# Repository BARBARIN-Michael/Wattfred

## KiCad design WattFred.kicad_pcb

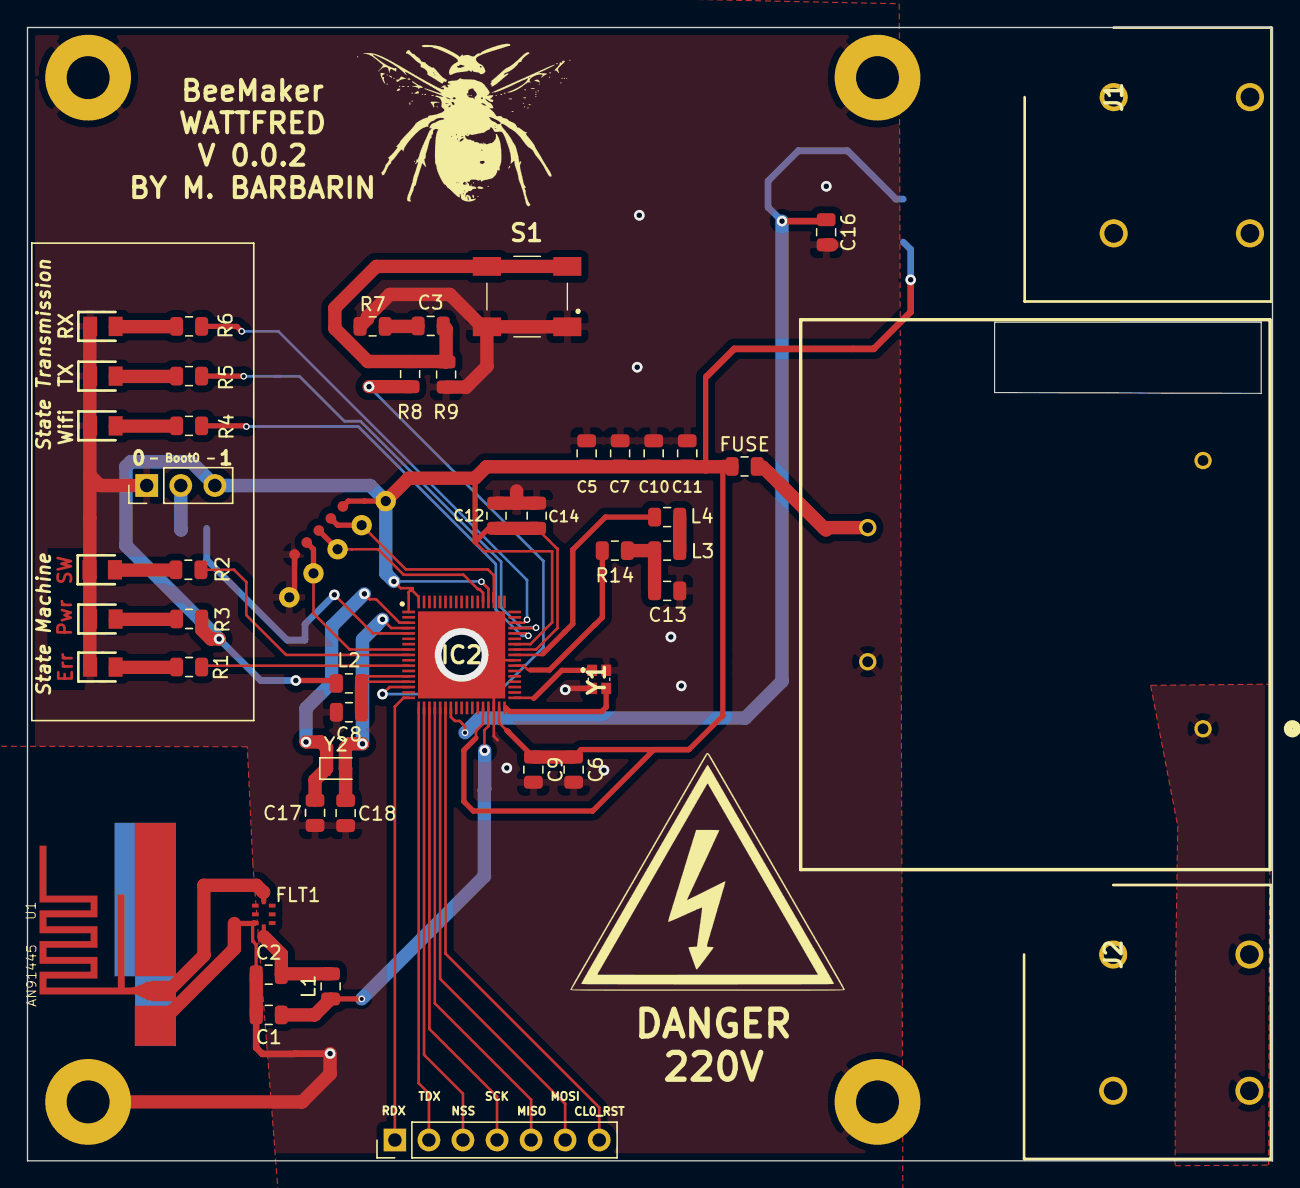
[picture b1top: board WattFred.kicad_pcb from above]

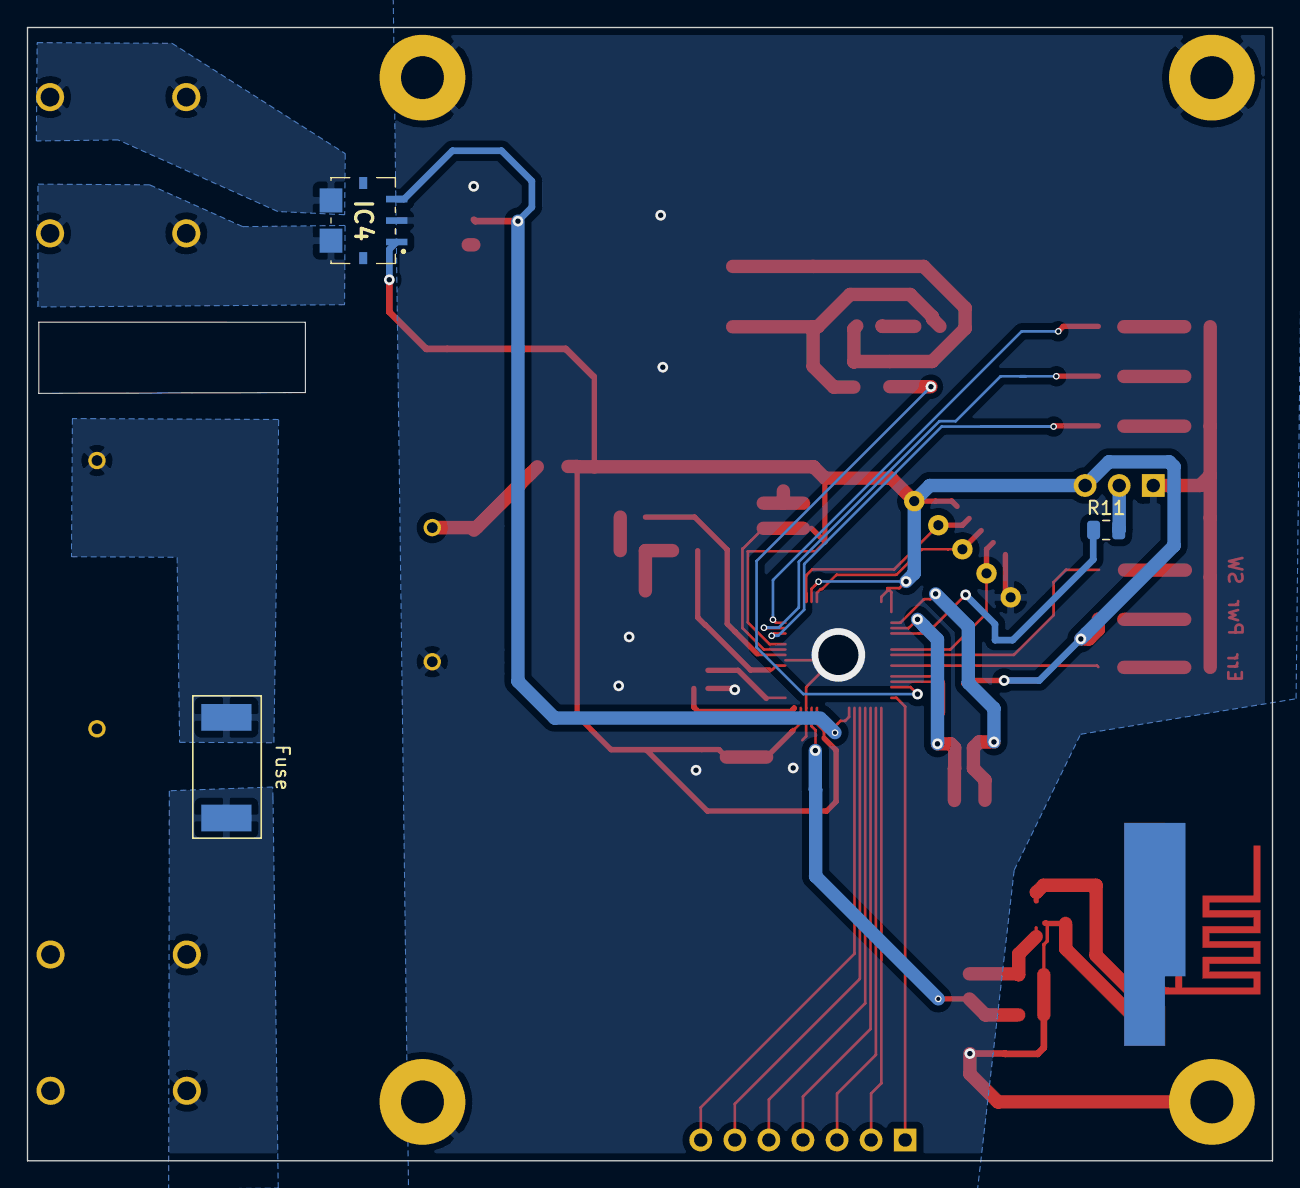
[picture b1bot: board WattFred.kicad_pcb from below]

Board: 2 copper layers, 92.8 x 84.5 mm, 51 parts (3 on the bottom side), 38 nets.

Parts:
- Boot0 -: PinHeader_1x03_P2.54mm_Vertical
C1: 0.8pF; C_0805_2012Metric
C2: 0.3pF; C_0805_2012Metric
C3, C5, C6, C7, C8, C10, C11, C14: 100nF; C_0805_2012Metric
C9: 100pF; C_0805_2012Metric
C12, C13: 4.7uF; C_0805_2012Metric
C16: CTRIM_Small; C_0805_2012Metric
C17, C18: 10p; C_0805_2012Metric
FLT1: LFL212G45TC1A007
FUSE: Fuse_0805_2012Metric
Fuse: FuseRS
IC2: STM32WB55RGV6; QFN40P800X800X100-69N-D
IC4: ACS781LLRTR-050U-T; ACS781LLRTR050BT
J1, J2: 691256610002-Bornier; SHDR4W120P1016_2X2_2032X1830X2940P
L1: 1.4 2.7nH; L_0805_2012Metric
L2: BLM31KN601SN1L; L_0805_2012Metric
L3, L4: 10nH; L_0805_2012Metric
LED1: Red; LEDC2012X70N
LED2: Green; LEDC2012X70N
LED3, LED5, LED6: Blue; LEDC2012X70N
LED4: White; LEDC2012X70N
R1, R4: 60; R_0805_2012Metric
R2, R3, R5, R6: 5; R_0805_2012Metric
R7: 100; R_0805_2012Metric
R8: 330; R_0805_2012Metric
R9: 220k; R_0805_2012Metric
R11: 10k; R_0805_2012Metric
R14: 0; R_0805_2012Metric
S1: WakeUp; LL3301FF065QJ
T1: 47206; 47203
U1: AN91445
U2: JTagPogoPin; JtagPogoPin
Y1: NX2016SA-32M-EXS00A-CS06465; NX2016SA32MEXS00ACS06465
Y2: 32.768KHz; Crystal_SMD_2012-2Pin_2.0x1.2mm

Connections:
Alim: - Boot0 -.3, C5.1, C6.1, C7.1, C9.1, C10.1, C11.1, C12.1, C14.1, FUSE.1, FUSE.2, IC2.1, IC2.30, IC2.33, IC2.44, IC2.45, IC2.55, IC2.68, IC4.1, L2.2, R3.1, T1.7, U2.1
BOOT0: IC2.5, R11.1
GND: - Boot0 -.1, C1.2, C2.2, C5.2, C6.2, C7.2, C8.2, C9.2, C10.2, C11.2, C12.2, C13.2, C14.2, C16.2, C17.2, C18.2, FLT1.1, IC2.32, IC2.42, IC2.69, IC4.2, LED1.1, LED2.1, LED3.1, LED4.1, LED5.1, LED6.1, R7.1, R9.2, S1.1, S1.2, T1.9, U1.2, U2.5, Y1.2, Y1.4
NRST: IC2.8, U2.4
unnamed: C2.1, FLT1.8, L1.2
unnamed: C3.1, R8.1, R9.1, S1.3, S1.4
unnamed: C3.2, R7.2
unnamed: C13.1, L3.2, R14.2
unnamed: FLT1.4, U1.1
unnamed: IC4.5, J1.1, J1.2
unnamed: IC4.6, J1.3, J1.4
unnamed: J2.2, J2.4, T1.1
unnamed: Fuse.1, Fuse.2, J2.1, J2.3, T1.5
unnamed: - Boot0 -.2, R11.2
unnamed: L3.1, L4.2
unnamed: LED1.2, R1.2
unnamed: LED2.2, R2.2
unnamed: LED3.2, R3.2
unnamed: LED4.2, R4.2
unnamed: LED5.2, R5.2
unnamed: LED6.2, R6.2
OSC32K_IN: C17.1, IC2.3, Y2.1
OSC32K_OUT: C18.1, IC2.4, Y2.2
PA0: IC2.15, R8.2
PA9: C16.1, IC2.24, IC4.3
PA13: IC2.54, U2.2
PA14: IC2.56, U2.3
PB13: IC2.47, R4.1
PB14: IC2.48, R5.1
PB15: IC2.49, R6.1
PC0: IC2.9, R2.1
PC2: IC2.11, R1.1
PF0_IN_32MHZ: IC2.35, Y1.1
PF0_OUT_32MHZ: IC2.34, Y1.3
RF1: C1.1, IC2.31, L1.1
VCCA: C8.1, IC2.13, IC2.14, L2.1
VFBSOUT: IC2.41, R14.1
VLXSMPS: IC2.43, L4.1

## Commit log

2019-12-06 V002 Wattfred project. Order done, need to test it
